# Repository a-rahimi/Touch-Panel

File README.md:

# Touch panel

A 12 × 15 inch panel of 12 copper pads that senses a hand above it, recognises a swipe
across the top row and back, and toggles a light. An MPR121 reads the pads and a XIAO
ESP32-C3 runs the firmware, which also reports the hand's position over Bluetooth LE.
`docs/DESIGN.md` explains how it works.

| Folder | What is in it |
|---|---|
| `cad/` | `tray.scad`, the 3D-printed tray that holds the pads and the boards, and in `cad/tools/` the scripts that make it printable |
| `docs/` | the design notes and the wiring diagram |
| `firmware/` | the ESP-IDF project for the XIAO, and in `firmware/tools/` the programs that talk to the board from a Mac |
| `pcb/` | the next version: the whole panel as one PCB with an ESP32-S3 and no MPR121, generated from Python (see `pcb/README.md`) |

## Printing the tray

`cad/tools/plate.sh` exports the four tiles from `cad/tray.scad` and puts them on four
plates of a Bambu Studio project for a Bambu Lab X2D, `cad/build/tray.3mf`. It needs
OpenSCAD and Bambu Studio installed where the script expects them.

## Flashing the firmware

The firmware needs ESP-IDF v6. The Wi-Fi network's name and password go in
`firmware/main/wifi_secrets.h`, which git ignores: copy `wifi_secrets.h.example` next
to it and fill it in. The build compiles them into the firmware, so the board can join
the network. The name of the Kasa switch to toggle is `KASA_ALIAS` in
`firmware/main/kasa.h`. The same firmware builds for either board; only the sensor
differs, and `firmware/tools/build.sh` picks it:

```
firmware/tools/build.sh xiao flash    # the XIAO ESP32-C3 with the MPR121
firmware/tools/build.sh pcb flash     # the ESP32-S3 PCB in pcb/
```

## Using it

`firmware/tools/monitor.py` shows what the board sees over USB.
`firmware/tools/ble_view.py` draws the hand's position from Bluetooth in a window, and
`firmware/tools/ble_talker.py` speaks the pad under the hand. Each runs with
[uv](https://docs.astral.sh/uv/), which installs its dependencies.

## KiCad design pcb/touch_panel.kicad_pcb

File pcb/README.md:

# The touch panel as one PCB

This replaces the printed tray, the copper stickers, the hand wiring and the two boards
with a single 2-layer board, 304.8 × 420 mm. The 12 pads are top copper under solder
mask, in the tray's grid. An ESP32-S3-WROOM-1 module senses them itself with its touch
inputs, so the board has no MPR121, which NXP has discontinued. The module sits in a
strip below the pads with USB-C, a 3.3 V regulator, reset and boot buttons and an LED.
Every part is on the back, so the front is only the pads and can lie flat against a
desk; the pads' traces stay on the back all the way to their resistors.

Everything here is generated from Python, so the design is in `tools/`, and the KiCad
files are its output:

| File | What it is |
|---|---|
| `tools/design.py` | every part, its footprint and LCSC number, and the net on each pin |
| `tools/make_schematic.py` | writes `touch_panel.kicad_sch` from it |
| `tools/make_board.py` | writes `touch_panel.kicad_pcb`: places the parts, draws the pad traces and zones, and routes the strip with `strip_router.py` |
| `tools/make_footprints.py` | writes the pad and shield-tap footprints in `touch_panel.pretty` |
| `tools/make_lib_tables.py` | writes the project's library tables |
| `tools/make_fab.py` | writes the gerbers, BOM, placement file and schematic PDF into `fab/` |

## The layout

- Each pad's signal leaves through a via in its corner to the bottom layer and runs down
  one of the two vertical gaps between pad columns, six traces to a gap, in an order that
  keeps them from crossing. Below the pads they return to the top layer as a bus, to a
  510 Ω resistor each above the module, as Espressif's hardware design guidelines ask.
- The bottom layer under the pads is a hatched shield driven by GPIO14, the only touch
  pin that can drive one. Driven with the same waveform as the pad being measured, it
  hides the pads from whatever is behind the board without loading them. The firmware
  can instead drive GPIO14 low, which grounds it, or leave it floating.
- The strip's copper is ground on both layers, starting 15 mm below the pads, so ground
  does not take the field the pads need. The module's antenna end is flush with the
  bottom edge, over its keepout.

## Rebuilding

The generators need KiCad 10. `make_board.py` and `make_fab.py` run in KiCad's own Python:

```
PY=~/Applications/KiCad/KiCad.app/Contents/Frameworks/Python.framework/Versions/Current/bin/python3
python3 pcb/tools/make_lib_tables.py
python3 pcb/tools/make_footprints.py
python3 pcb/tools/make_schematic.py
$PY pcb/tools/make_board.py
python3 pcb/tools/make_fab.py
```

The schematic passes KiCad's electrical rules check, and the board passes its design
rules check with the schematic parity check on, with only silkscreen warnings and a
note that the module's footprint differs from the library's: its 0.2 mm thermal vias
are removed, because JLCPCB's standard minimum hole is 0.3 mm.

## Ordering from JLCPCB

Upload `fab/touch_panel_gerbers.zip` as a 2-layer, 1.6 mm board, and for assembly on the
bottom side, `fab/touch_panel_bom.csv` and `fab/touch_panel_cpl.csv`. Before paying, check
each part's rotation in JLCPCB's assembly preview: KiCad's footprint orientation and
JLCPCB's part orientation differ for some parts, often the SOT-23 and the USB-C
connector, and the files here have not been corrected for that.

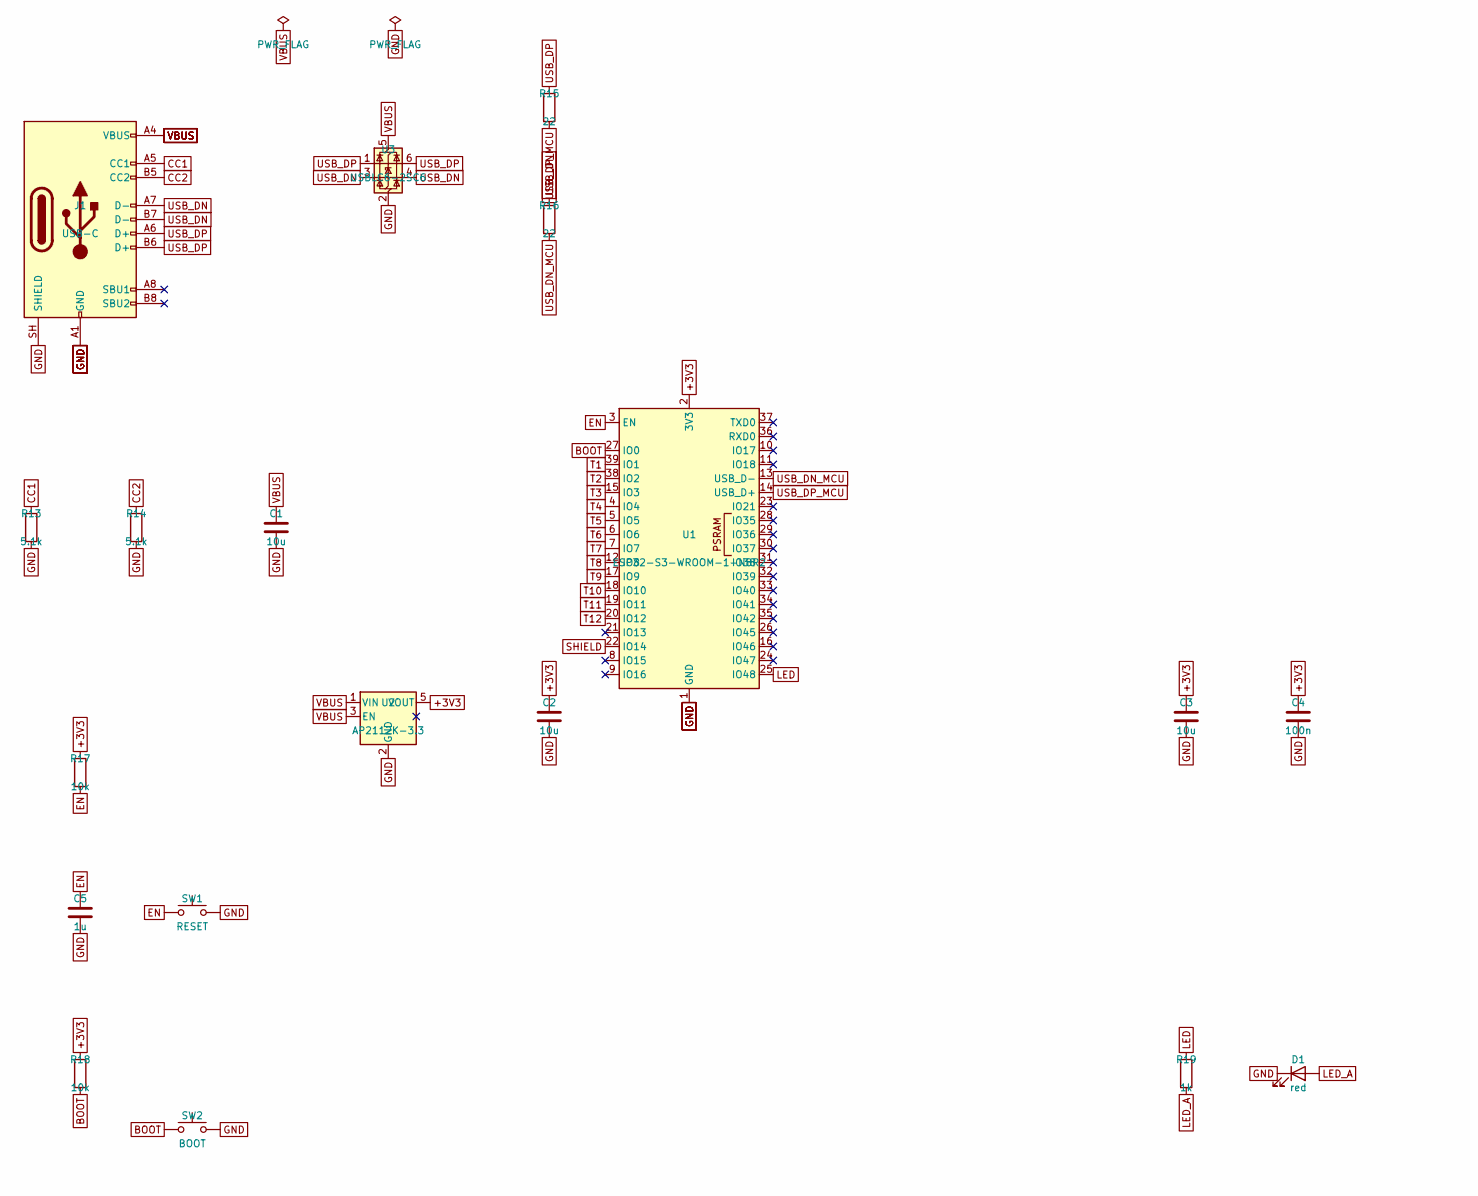
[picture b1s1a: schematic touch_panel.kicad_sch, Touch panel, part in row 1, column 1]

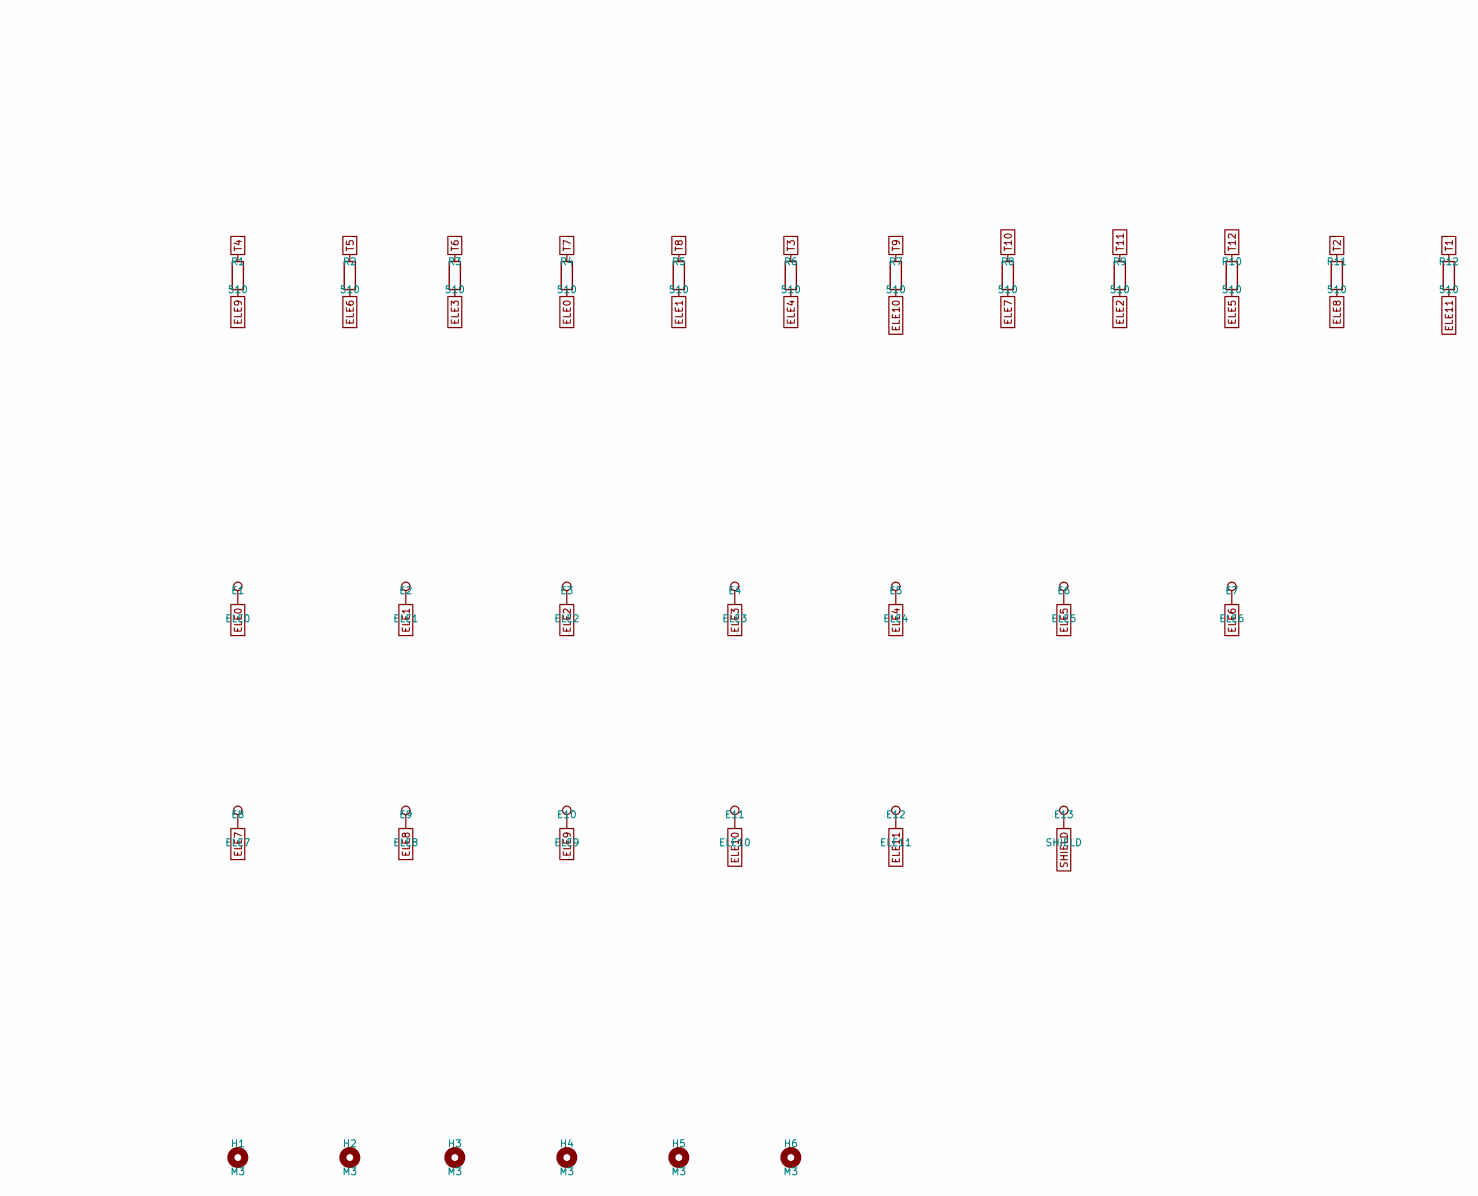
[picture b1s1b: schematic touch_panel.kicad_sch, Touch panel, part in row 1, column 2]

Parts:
C1, C2, C3: 10u; C_0603_1608Metric; LCSC C19702
C4: 100n; C_0402_1005Metric; LCSC C1525
C5: 1u; C_0402_1005Metric; LCSC C52923
D1: red; LED_0603_1608Metric; LCSC C2286
E1: ELE0; Electrode
E2: ELE1; Electrode
E3: ELE2; Electrode
E4: ELE3; Electrode
E5: ELE4; Electrode
E6: ELE5; Electrode
E7: ELE6; Electrode
E8: ELE7; Electrode
E9: ELE8; Electrode
E10: ELE9; Electrode
E11: ELE10; Electrode
E12: ELE11; Electrode
E13: SHIELD; ShieldTap
H1, H2, H3, H4, H5, H6: M3; MountingHole_3.2mm_M3
J1: USB-C; USB_C_Receptacle_HRO_TYPE-C-31-M-12; LCSC C165948
R1, R2, R3, R4, R5, R6, R7, R8, R9, R10, R11, R12: 510; R_0402_1005Metric; LCSC C25123
R13, R14: 5.1k; R_0402_1005Metric; LCSC C25905
R15, R16: 22; R_0402_1005Metric; LCSC C25092
R17, R18: 10k; R_0402_1005Metric; LCSC C25744
R19: 1k; R_0402_1005Metric; LCSC C11702
SW1: RESET; SW_Push_1P1T_XKB_TS-1187A; LCSC C318884
SW2: BOOT; SW_Push_1P1T_XKB_TS-1187A; LCSC C318884
U1: ESP32-S3-WROOM-1-N8R2; ESP32-S3-WROOM-1; LCSC C2913204
U2: AP2112K-3.3; SOT-23-5; LCSC C51118
U3: USBLC6-2SC6; SOT-23-6; LCSC C7519

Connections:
+3V3: C2.1, C3.1, C4.1, R17.1, R18.1, U1.2 (3V3), U2.5 (VOUT)
BOOT: R18.2, SW2.1, U1.27 (IO0)
CC1: J1.A5 (CC1), R13.1
CC2: J1.B5 (CC2), R14.1
ELE0: E1.1, R4.2
ELE1: E2.1, R5.2
ELE2: E3.1, R9.2
ELE3: E4.1, R3.2
ELE4: E5.1, R6.2
ELE5: E6.1, R10.2
ELE6: E7.1, R2.2
ELE7: E8.1, R8.2
ELE8: E9.1, R11.2
ELE9: E10.1, R1.2
ELE10: E11.1, R7.2
ELE11: E12.1, R12.2
EN: C5.1, R17.2, SW1.1, U1.3 (EN)
GND: C1.2, C2.2, C3.2, C4.2, C5.2, D1.1 (K), J1.A1 (GND), J1.A12 (GND), J1.B1 (GND), J1.B12 (GND), J1.SH (SHIELD), R13.2, R14.2, SW1.2, SW2.2, U1.1 (GND), U1.40 (GND), U1.41 (GND), U2.2 (GND), U3.2 (GND)
LED: R19.1, U1.25 (IO48)
LED_A: D1.2 (A), R19.2
SHIELD: E13.1, U1.22 (IO14)
T1: R12.1, U1.39 (IO1)
T2: R11.1, U1.38 (IO2)
T3: R6.1, U1.15 (IO3)
T4: R1.1, U1.4 (IO4)
T5: R2.1, U1.5 (IO5)
T6: R3.1, U1.6 (IO6)
T7: R4.1, U1.7 (IO7)
T8: R5.1, U1.12 (IO8)
T9: R7.1, U1.17 (IO9)
T10: R8.1, U1.18 (IO10)
T11: R9.1, U1.19 (IO11)
T12: R10.1, U1.20 (IO12)
USB_DN: J1.A7 (D-), J1.B7 (D-), R16.1, U3.3 (I/O2), U3.4 (I/O2)
USB_DN_MCU: R16.2, U1.13 (USB_D-)
USB_DP: J1.A6 (D+), J1.B6 (D+), R15.1, U3.1 (I/O1), U3.6 (I/O1)
USB_DP_MCU: R15.2, U1.14 (USB_D+)
VBUS: C1.1, J1.A4 (VBUS), J1.A9 (VBUS), J1.B4 (VBUS), J1.B9 (VBUS), U2.1 (VIN), U2.3 (EN), U3.5 (VBUS)

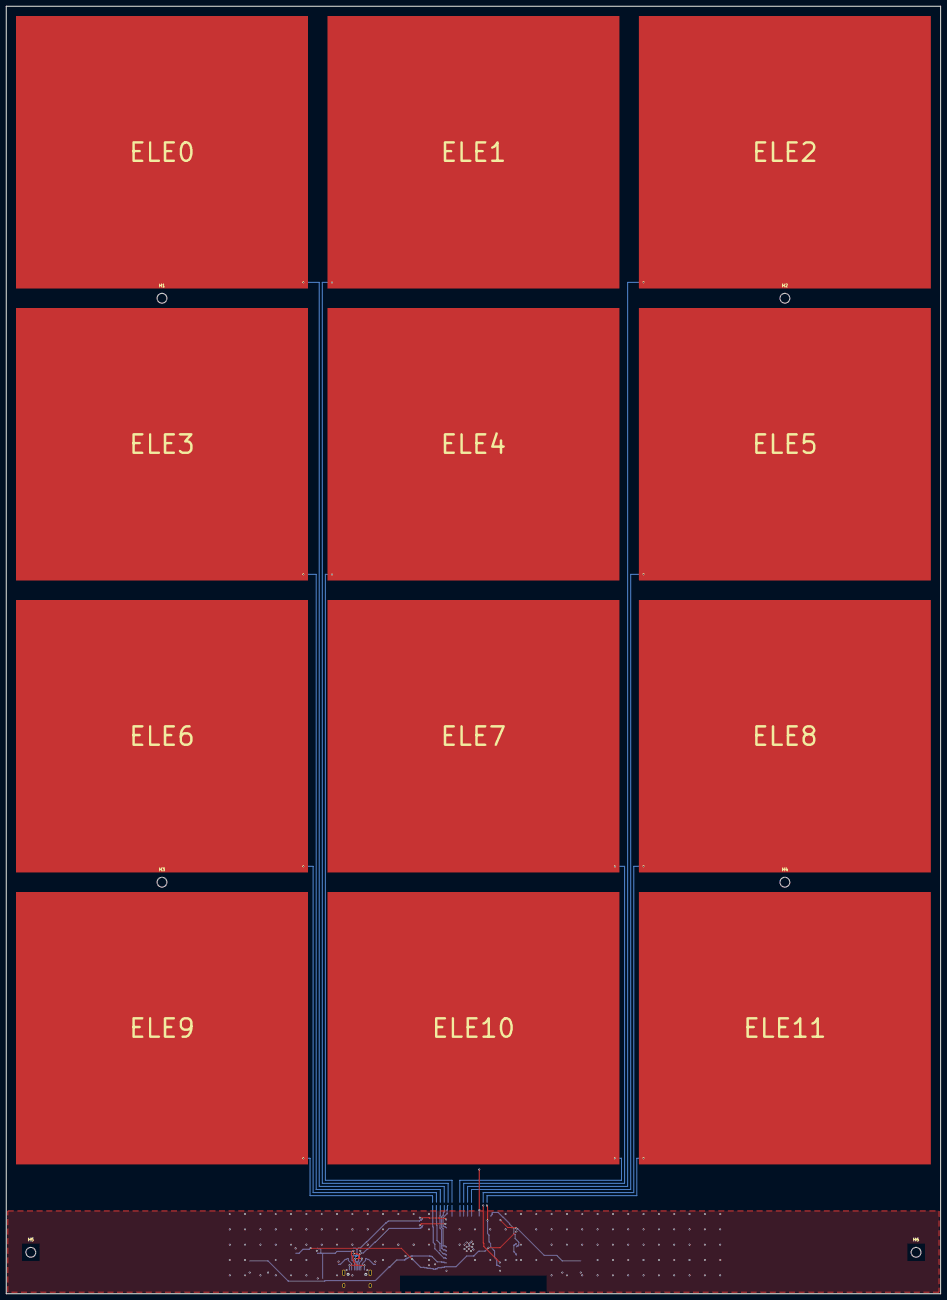
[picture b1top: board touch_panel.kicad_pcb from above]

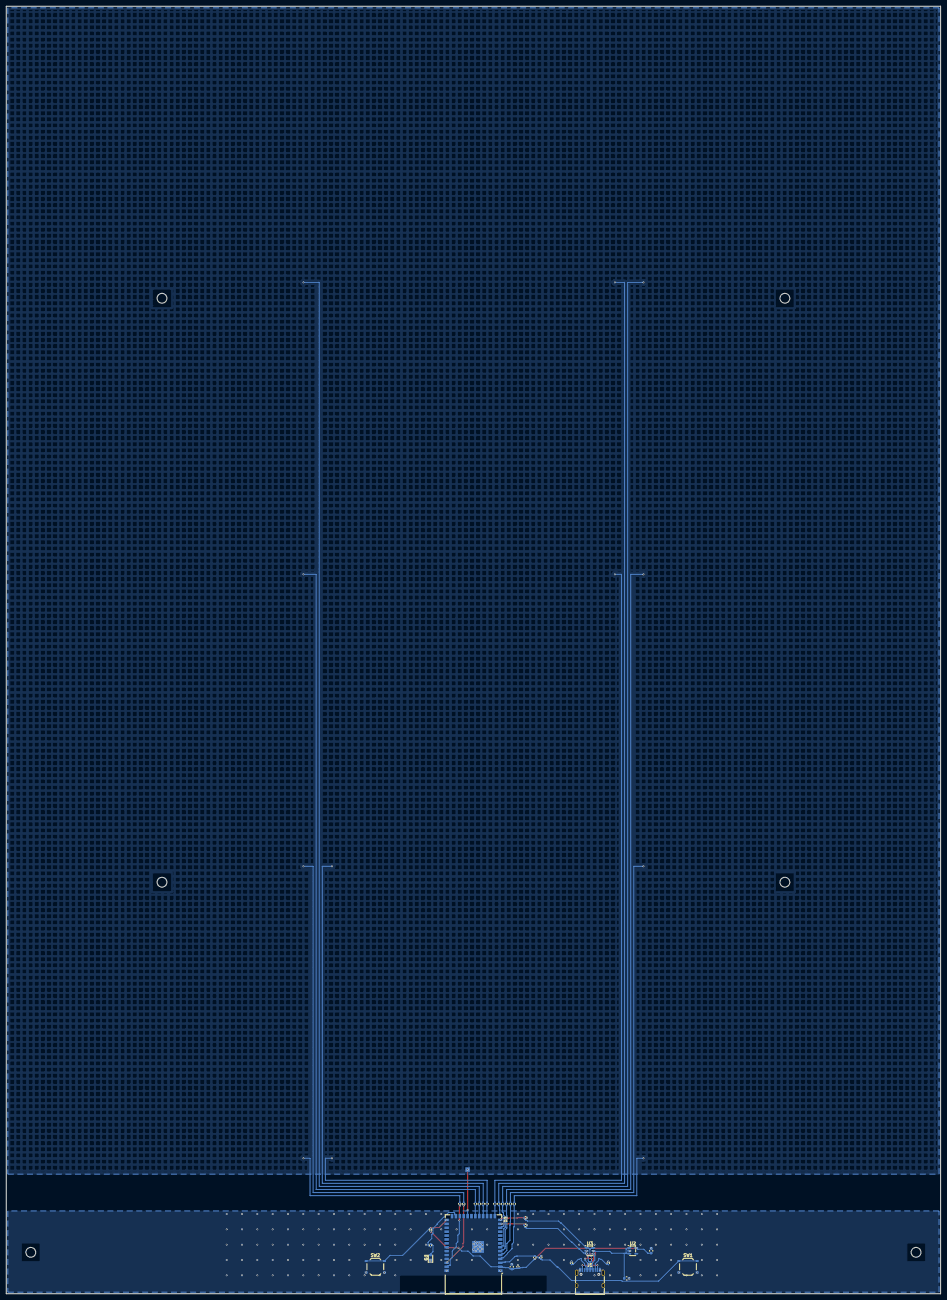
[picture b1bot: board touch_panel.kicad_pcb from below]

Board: 2 copper layers, 304.8 x 420.0 mm, 50 parts (32 on the bottom side), 38 nets.
